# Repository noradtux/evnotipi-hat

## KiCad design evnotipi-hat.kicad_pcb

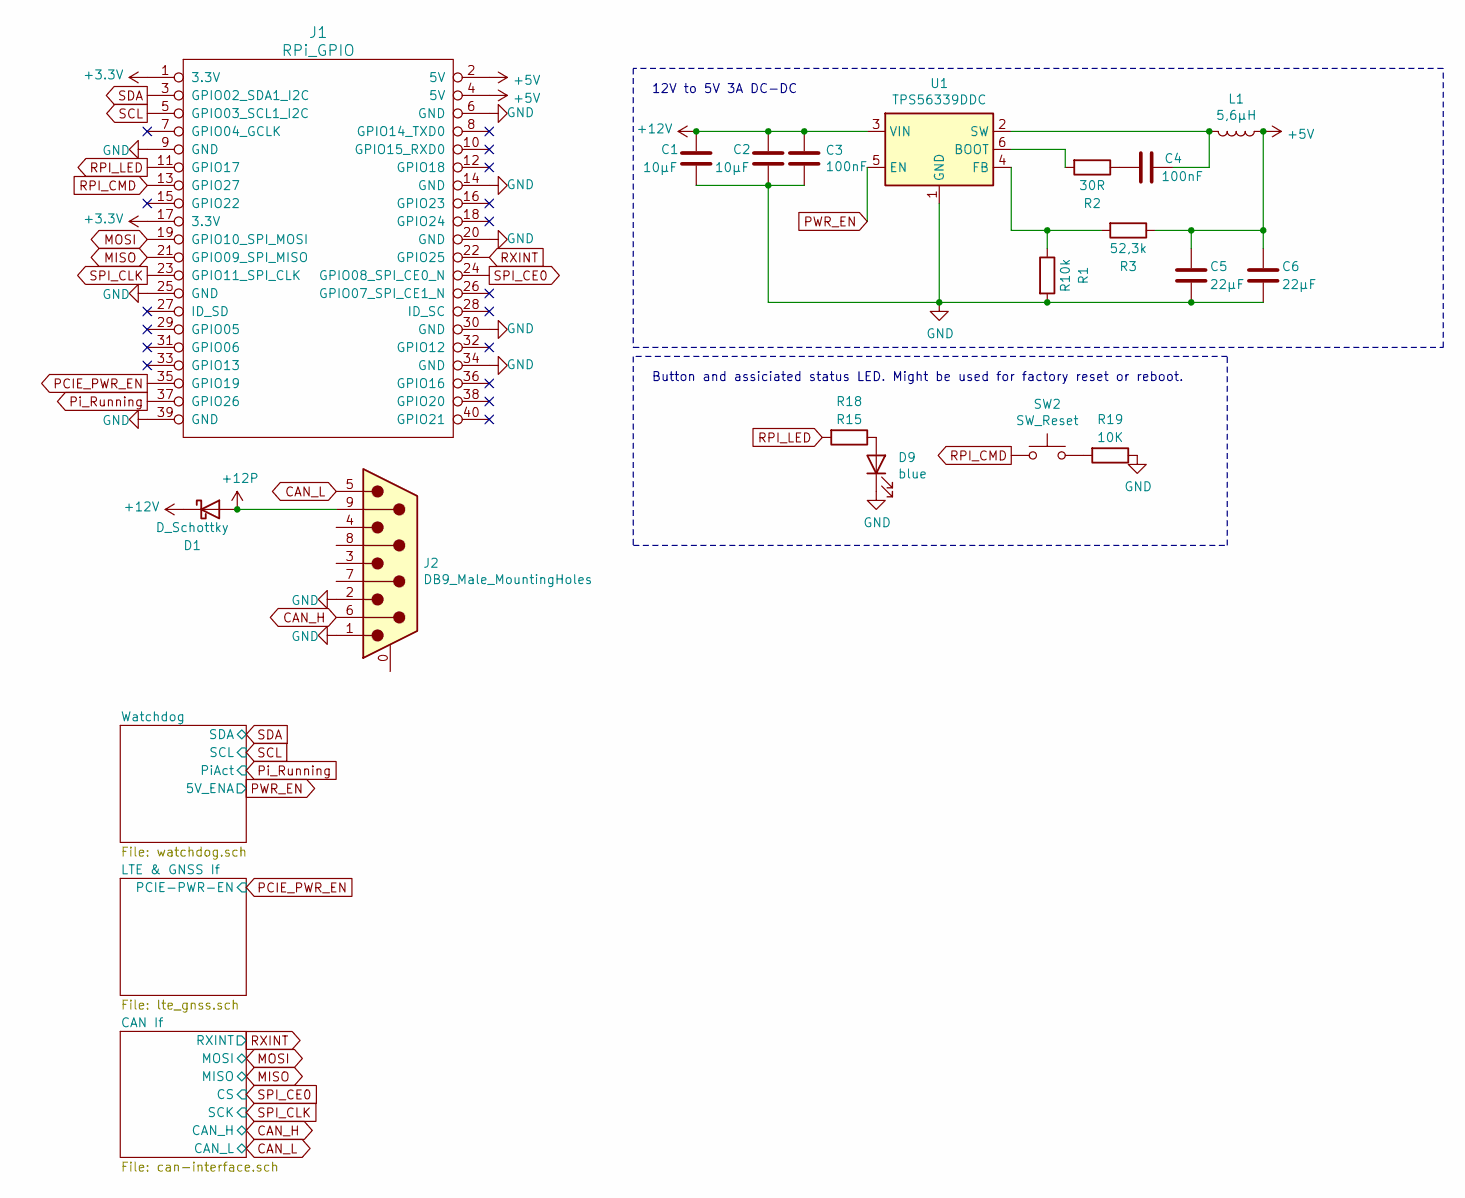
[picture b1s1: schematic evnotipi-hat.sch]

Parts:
C1, C2: 10µF; C_0805_2012Metric_Pad1.15x1.40mm_HandSolder
C3, C4: 100nF; C_0805_2012Metric_Pad1.15x1.40mm_HandSolder
C5, C6: 22µF; C_0805_2012Metric_Pad1.15x1.40mm_HandSolder
D1: D_Schottky; D_SOD-128
D9: blue; LED_0603_1608Metric
J1: RPi_GPIO; Samtec_HLE-120-02-xxx-DV-BE-A_2x20_RPi_Top
J2: DB9_Male_MountingHoles; DSUB-9_Male_Horizontal_P2.77x2.84mm_EdgePinOffset4.94mm_Hou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
L1: 5,6µH; L_Coilcraft_XAL60xx_6.36x6.56mm
R1: R10k; R_0603_1608Metric_Pad1.05x0.95mm_HandSolder
R2: 30R; R_0603_1608Metric_Pad1.05x0.95mm_HandSolder
R3: 52,3k; R_0603_1608Metric_Pad1.05x0.95mm_HandSolder
R18: R15; R_0603_1608Metric_Pad1.05x0.95mm_HandSolder
R19: 10K; R_0603_1608Metric_Pad1.05x0.95mm_HandSolder
SW2: SW_Reset; SW_SPST_B3U-1000P
U1: TPS56339DDC; SOT-23-6

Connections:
+5V: C5.1, C6.1, J1.2 (5V), J1.4 (5V), L1.1, R3.1; also elsewhere on the board
+12P: D1.2 (A), J2.9; also elsewhere on the board
+12V: C1.1, C2.1, C3.1, D1.1 (K), U1.3 (VIN); also elsewhere on the board
CAN_H: J2.6; also elsewhere on the board
CAN_L: J2.5; also elsewhere on the board
GND: C1.2, C2.2, C3.2, C5.2, C6.2, D9.1 (K), J1.6 (GND), J1.9 (GND), J1.14 (GND), J1.20 (GND), J1.25 (GND), J1.30 (GND), J1.34 (GND), J1.39 (GND), J2.1, J2.2, R1.2, R19.1, U1.1 (GND); also elsewhere on the board
MISO: J1.21 (GPIO09_SPI_MISO); also elsewhere on the board
MOSI: J1.19 (GPIO10_SPI_MOSI); also elsewhere on the board
unnamed: C4.1, L1.2, U1.2 (SW)
unnamed: C4.2, R2.1
unnamed: D9.2 (A), R18.1
unnamed: R1.1, R3.2, U1.4 (FB)
unnamed: R2.2, U1.6 (BOOT)
unnamed: R19.2, SW2.2
PCIE_PWR_EN: J1.35 (GPIO19); also elsewhere on the board
PWR_EN: U1.5 (EN); also elsewhere on the board
Pi_Running: J1.37 (GPIO26); also elsewhere on the board
RPI_CMD: J1.13 (GPIO27), SW2.1
RPI_LED: J1.11 (GPIO17), R18.2
RXINT: J1.22 (GPIO25); also elsewhere on the board
SCL: J1.5 (GPIO03_SCL1_I2C); also elsewhere on the board
SDA: J1.3 (GPIO02_SDA1_I2C); also elsewhere on the board
SPI_CE0: J1.24 (GPIO08_SPI_CE0_N); also elsewhere on the board
SPI_CLK: J1.23 (GPIO11_SPI_CLK); also elsewhere on the board

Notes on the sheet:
12V to 5V 3A DC-DC
Button and assiciated status LED. Might be used for factory reset or reboot.

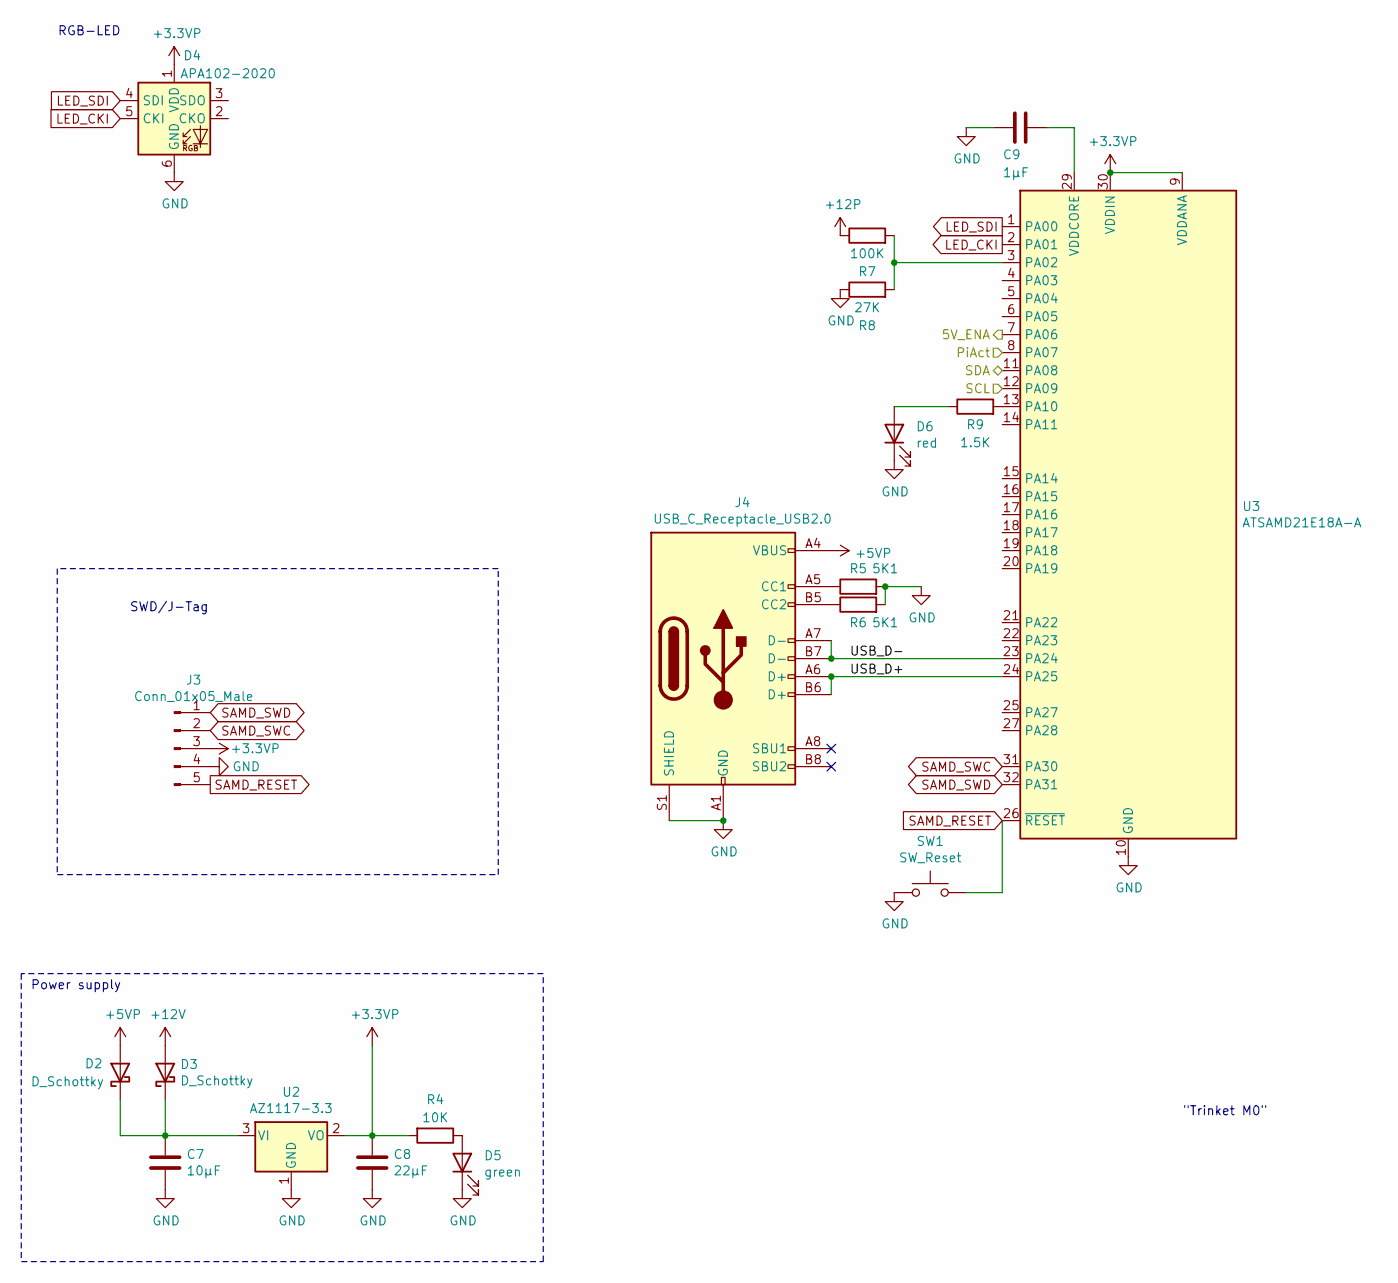
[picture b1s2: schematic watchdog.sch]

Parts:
C7: 10µF; C_0805_2012Metric_Pad1.15x1.40mm_HandSolder
C8: 22µF; C_0805_2012Metric_Pad1.15x1.40mm_HandSolder
C9: 1µF; C_0805_2012Metric_Pad1.15x1.40mm_HandSolder
D2, D3: D_Schottky; D_SOD-128
D4: APA102-2020; LED-APA102-2020
D5: green; LED_0603_1608Metric
D6: red; LED_0603_1608Metric
J3: Conn_01x05_Male; Molex_PicoBlade_53047-0510_1x05_P1.25mm_Vertical
J4: USB_C_Receptacle_USB2.0; USB_C_Receptacle_HRO_TYPE-C-31-M-12
R4: 10K; R_0603_1608Metric_Pad1.05x0.95mm_HandSolder
R5, R6: 5K1; R_0603_1608Metric_Pad1.05x0.95mm_HandSolder
R7: 100K; R_0603_1608Metric_Pad1.05x0.95mm_HandSolder
R8: 27K; R_0603_1608Metric_Pad1.05x0.95mm_HandSolder
R9: 1.5K; R_0603_1608Metric_Pad1.05x0.95mm_HandSolder
SW1: SW_Reset; SW_SPST_B3U-1000P
U2: AZ1117-3.3; SOT-223
U3: ATSAMD21E18A-A; TQFP-32_7x7mm_P0.8mm

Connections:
+3.3VP: C8.1, D4.1 (VDD), J3.3, R4.2, U2.2 (VO), U3.9 (VDDANA), U3.30 (VDDIN)
+5VP: D2.2 (A), J4.A4 (VBUS), J4.A9 (VBUS), J4.B4 (VBUS), J4.B9 (VBUS)
+12P: R7.1; also elsewhere on the board
+12V: D3.2 (A); also elsewhere on the board
/Watchdog/USB_D+: J4.A6 (D+), J4.B6 (D+), U3.24 (PA25)
/Watchdog/USB_D-: J4.A7 (D-), J4.B7 (D-), U3.23 (PA24)
GND: C7.2, C8.2, C9.1, D4.6 (GND), D5.1 (K), D6.1 (K), J3.4, J4.A1 (GND), J4.A12 (GND), J4.B1 (GND), J4.B12 (GND), J4.S1 (SHIELD), R5.2, R6.2, R8.1, SW1.1, U2.1 (GND), U3.10 (GND), U3.28 (GND); also elsewhere on the board
LED_CKI: D4.5 (CKI), U3.2 (PA01)
LED_SDI: D4.4 (SDI), U3.1 (PA00)
unnamed: C7.1, D2.1 (K), D3.1 (K), U2.3 (VI)
unnamed: C9.2, U3.29 (VDDCORE)
unnamed: D5.2 (A), R4.1
unnamed: D6.2 (A), R9.1
unnamed: J4.A5 (CC1), R5.1
unnamed: J4.B5 (CC2), R6.1
unnamed: R7.2, R8.2, U3.3 (PA02)
unnamed: R9.2, U3.13 (PA10)
PWR_EN: U3.7 (PA06); also elsewhere on the board
Pi_Running: U3.8 (PA07); also elsewhere on the board
SAMD_RESET: J3.5, SW1.2, U3.26 (~RESET)
SAMD_SWC: J3.2, U3.31 (PA30)
SAMD_SWD: J3.1, U3.32 (PA31)
SCL: U3.12 (PA09); also elsewhere on the board
SDA: U3.11 (PA08); also elsewhere on the board

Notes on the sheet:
"Trinket M0"
Power supply
SWD/J-Tag
RGB-LED

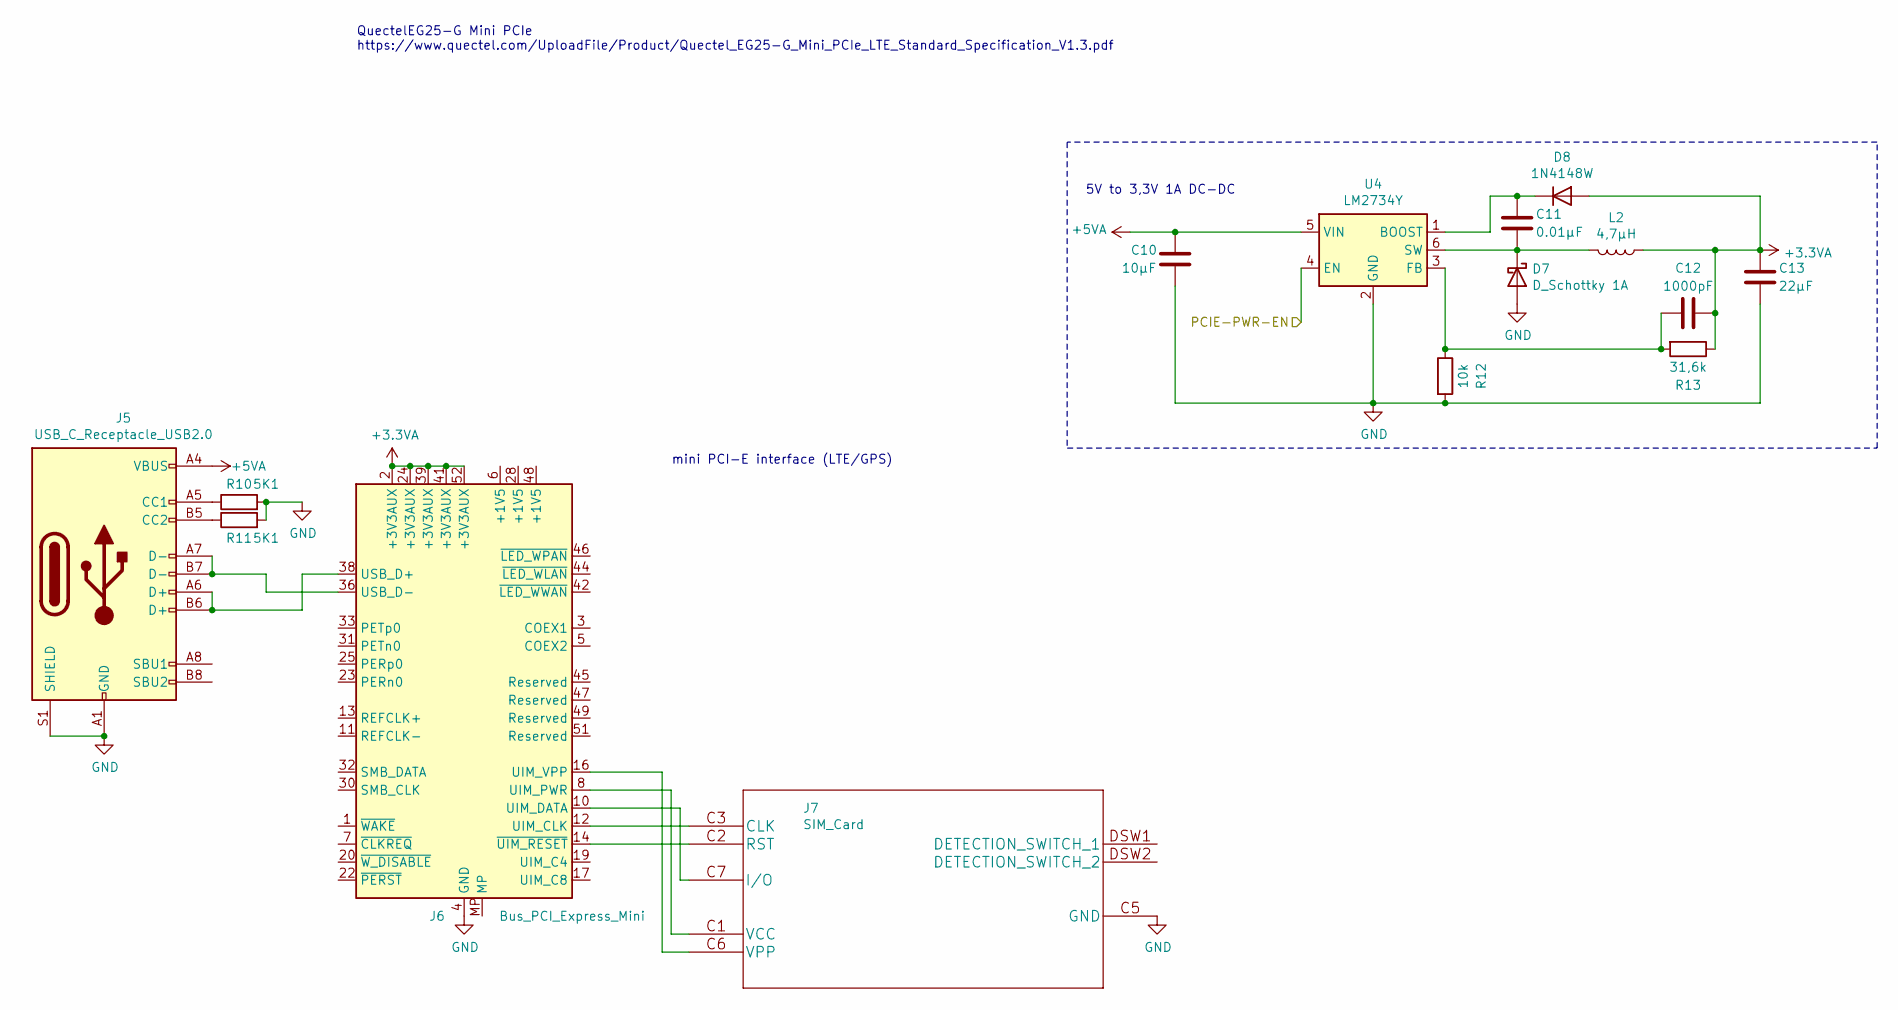
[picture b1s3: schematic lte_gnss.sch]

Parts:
C10: 10µF; C_0805_2012Metric_Pad1.15x1.40mm_HandSolder
C11: 0.01µF; C_0805_2012Metric_Pad1.15x1.40mm_HandSolder
C12: 1000pF; C_0805_2012Metric_Pad1.15x1.40mm_HandSolder
C13: 22µF; C_0805_2012Metric_Pad1.15x1.40mm_HandSolder
D7: D_Schottky 1A; D_SOD-128
D8: 1N4148W; D_SOD-128
J5: USB_C_Receptacle_USB2.0; USB_C_Receptacle_HRO_TYPE-C-31-M-12
J6: Bus_PCI_Express_Mini; BUS_PCI_Express_Mini_Full
J7: SIM_Card; SF56S006V4BR2000
L2: 4,7µH; L_Coilcraft_XAL60xx_6.36x6.56mm
R10, R11: 5K1; R_0603_1608Metric_Pad1.05x0.95mm_HandSolder
R12: 10k; R_0603_1608Metric_Pad1.05x0.95mm_HandSolder
R13: 31,6k; R_0603_1608Metric_Pad1.05x0.95mm_HandSolder
U4: LM2734Y; TSOT-23-6_HandSoldering

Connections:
+3.3VA: C12.1, C13.1, D8.2 (A), J6.2 (+3V3AUX), J6.24 (+3V3AUX), J6.39 (+3V3AUX), J6.41 (+3V3AUX), J6.52 (+3V3AUX), L2.1, R13.1
+5VA: C10.1, J5.A4 (VBUS), J5.A9 (VBUS), J5.B4 (VBUS), J5.B9 (VBUS), U4.5 (VIN)
GND: C10.2, C13.2, D7.2 (A), J5.A1 (GND), J5.A12 (GND), J5.B1 (GND), J5.B12 (GND), J5.S1 (SHIELD), J6.4 (GND), J6.9 (GND), J6.15 (GND), J6.18 (GND), J6.21 (GND), J6.26 (GND), J6.27 (GND), J6.29 (GND), J6.34 (GND), J6.35 (GND), J6.37 (GND), J6.40 (GND), J6.43 (GND), J6.50 (GND), J7.C5 (GND), R10.2, R11.2, R12.2, U4.2 (GND); also elsewhere on the board
unnamed: C11.1, D8.1 (K), U4.1 (BOOST)
unnamed: C11.2, D7.1 (K), L2.2, U4.6 (SW)
unnamed: C12.2, R12.1, R13.2, U4.3 (FB)
unnamed: J5.A5 (CC1), R10.1
unnamed: J5.A6 (D+), J5.B6 (D+), J6.38 (USB_D+)
unnamed: J5.A7 (D-), J5.B7 (D-), J6.36 (USB_D-)
unnamed: J5.B5 (CC2), R11.1
unnamed: J6.8 (UIM_PWR), J7.C1 (VCC)
unnamed: J6.10 (UIM_DATA), J7.C7 (I/O)
unnamed: J6.12 (UIM_CLK), J7.C3 (CLK)
unnamed: J6.14 (~UIM_RESET), J7.C2 (RST)
unnamed: J6.16 (UIM_VPP), J7.C6 (VPP)
PCIE_PWR_EN: U4.4 (EN); also elsewhere on the board

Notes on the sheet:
QuectelEG25-G Mini PCIe https://www.quectel.com/UploadFile/Product/Quectel_EG25-G_Mini_PCIe_LTE_Standard_Specification_V1.3.pdf
mini PCI-E interface (LTE/GPS)
5V to 3,3V 1A DC-DC

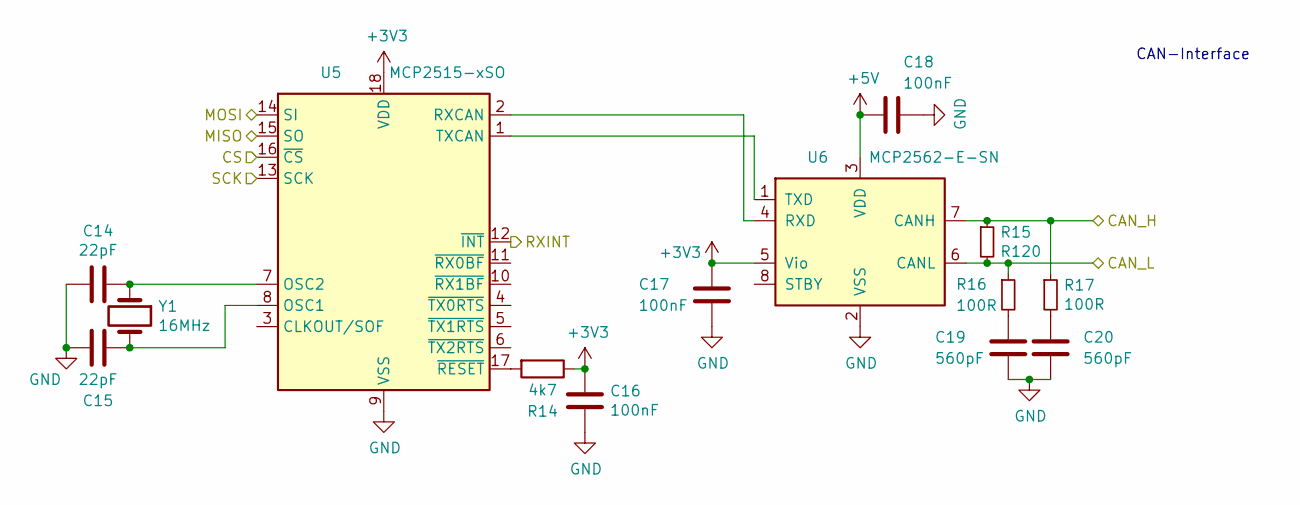
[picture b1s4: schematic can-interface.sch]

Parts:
C14, C15: 22pF; C_0805_2012Metric_Pad1.15x1.40mm_HandSolder
C16, C17, C18: 100nF; C_0805_2012Metric_Pad1.15x1.40mm_HandSolder
C19, C20: 560pF; C_0805_2012Metric_Pad1.15x1.40mm_HandSolder
R14: 4k7; R_0603_1608Metric_Pad1.05x0.95mm_HandSolder
R15: R120; R_0603_1608Metric_Pad1.05x0.95mm_HandSolder
R16, R17: 100R; R_0603_1608Metric_Pad1.05x0.95mm_HandSolder
U5: MCP2515-xSO; SOIC-18W_7.5x11.6mm_P1.27mm
U6: MCP2562-E-SN; SOIC-8_3.9x4.9mm_P1.27mm
Y1: 16MHz; Crystal_SMD_Abracon_ABM3-2Pin_5.0x3.2mm

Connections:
+5V: C18.1, U6.3 (VDD); also elsewhere on the board
CAN_H: R15.1, R17.1, U6.7 (CANH); also elsewhere on the board
CAN_L: R15.2, R16.1, U6.6 (CANL); also elsewhere on the board
GND: C14.2, C15.2, C16.1, C17.1, C18.2, C19.1, C20.1, U5.9 (VSS), U6.2 (VSS); also elsewhere on the board
MISO: U5.15 (SO); also elsewhere on the board
MOSI: U5.14 (SI); also elsewhere on the board
unnamed: C14.1, U5.7 (OSC2), Y1.1
unnamed: C15.1, U5.8 (OSC1), Y1.2
unnamed: C19.2, R16.2
unnamed: C20.2, R17.2
unnamed: R14.2, U5.17 (~RESET)
unnamed: U5.1 (TXCAN), U6.1 (TXD)
unnamed: U5.2 (RXCAN), U6.4 (RXD)
RXINT: U5.12 (~INT); also elsewhere on the board
SPI_CE0: U5.16 (~CS); also elsewhere on the board
SPI_CLK: U5.13 (SCK); also elsewhere on the board

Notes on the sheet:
CAN-Interface

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
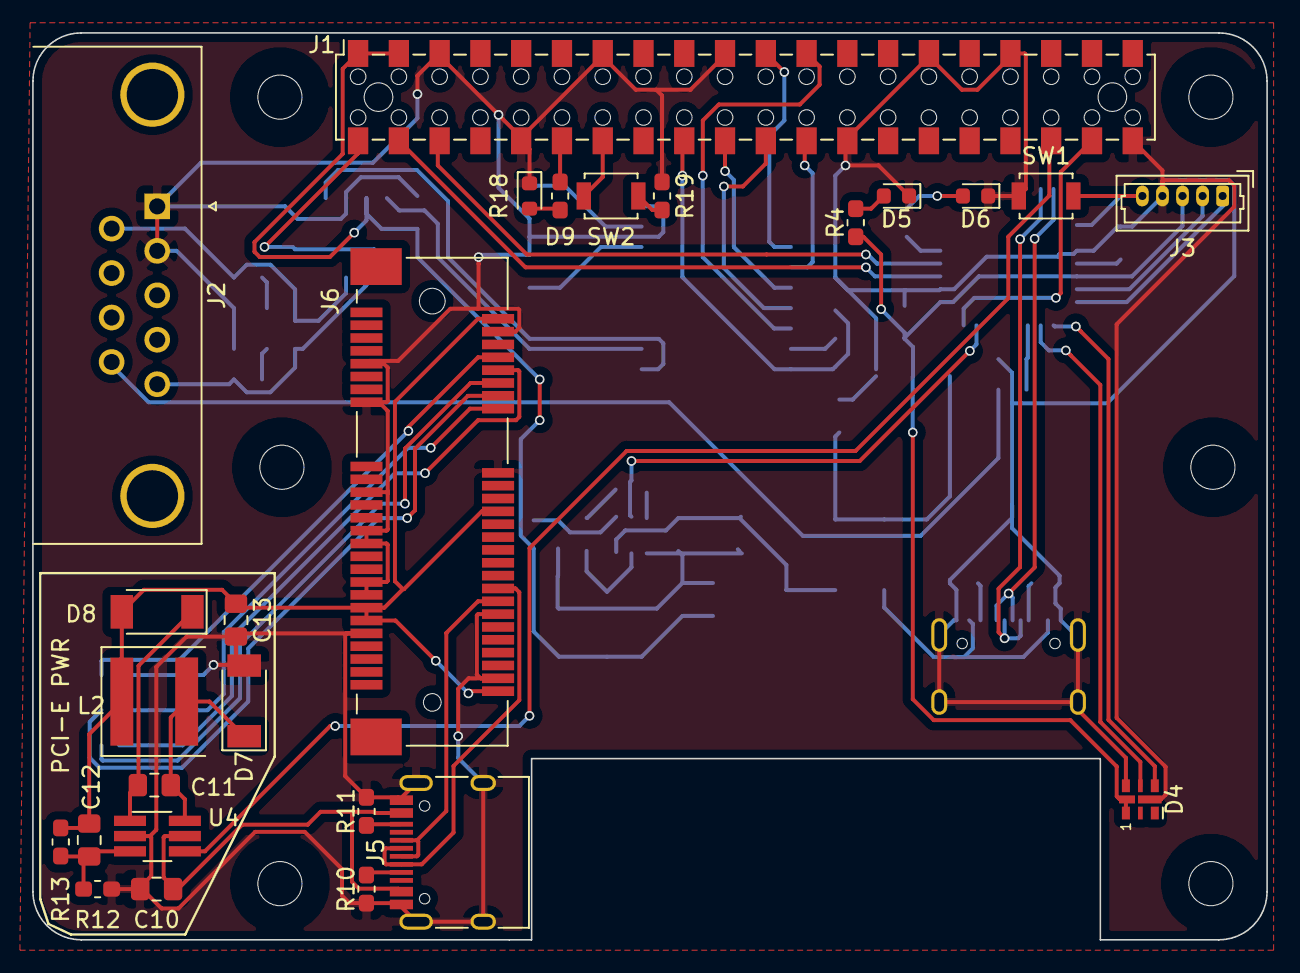
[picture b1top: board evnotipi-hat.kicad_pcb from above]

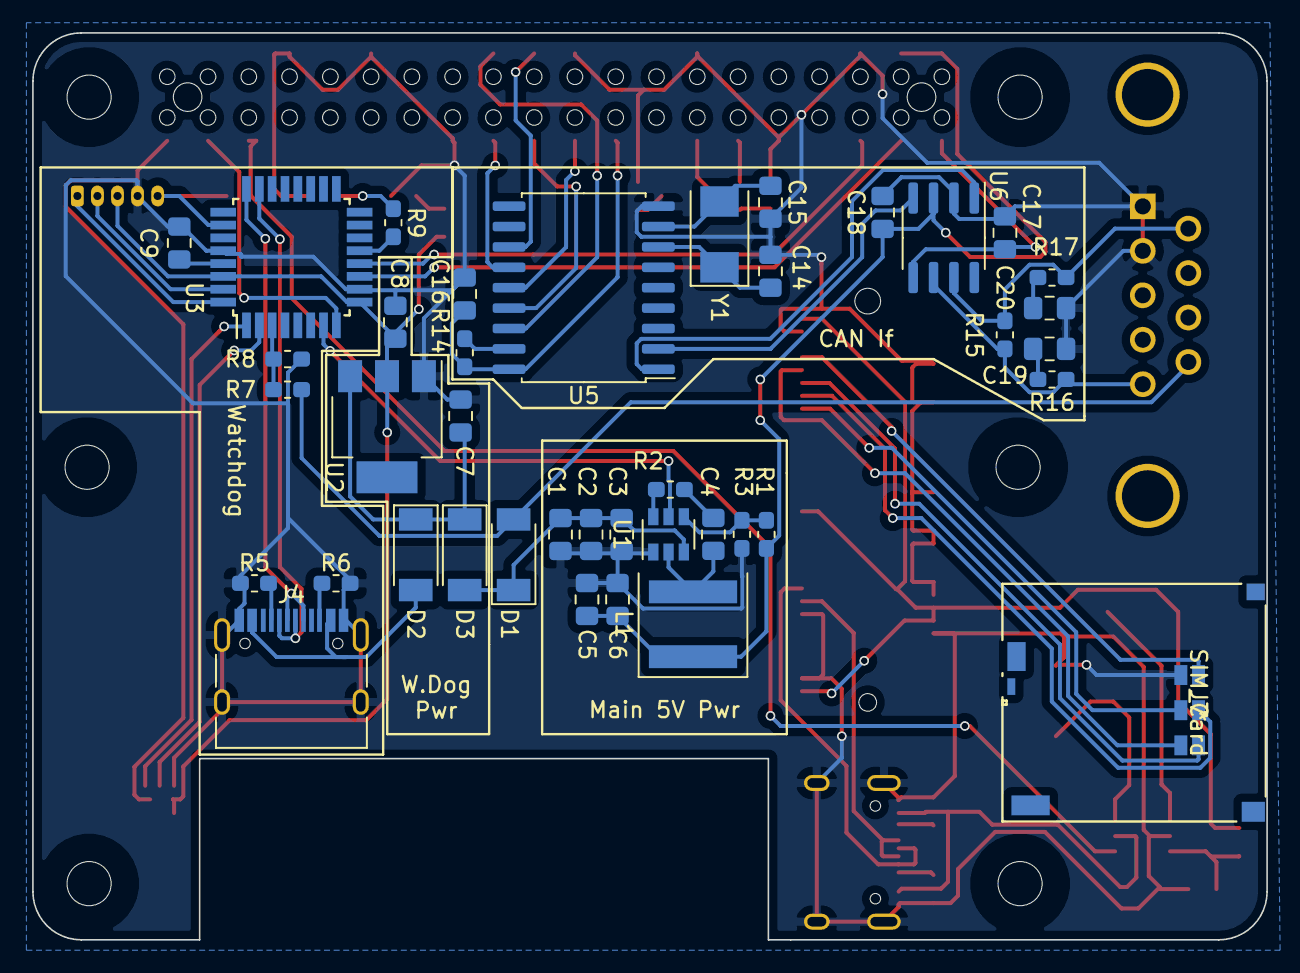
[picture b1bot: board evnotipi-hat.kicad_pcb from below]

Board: 2 copper layers, 76.9 x 56.5 mm, 66 parts (40 on the bottom side), 63 nets.

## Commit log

2020-08-14 Redesigned again. Prototype 1

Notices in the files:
parts and their libraries:
Copyright 2016 Accelerated Designs. All rights reserved.
